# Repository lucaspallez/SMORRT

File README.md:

# SMORRT
Smart Management of Rocket Recovery and Telemetry

Avionics PCB for High-Power Rocketry

Embedded Software for this board available here: https://github.com/lucaspallez/SMORRT_Software
Compatible Ground Station PCB: https://github.com/lucaspallez/GRUND

## Features
- Computation: Teensy 4.1
- Telemetry: RFM95W LoRa Module (with SMA connector)
- IMU: MPU 6050 Breakout
- Barometer: BMP 280 Breakout
- GPS: Ublox NEO-M8J Module (with SMA connector)
- Data logging: 1Mbit FRAM IC + Teensy SD Card slot with locking screw
- Power Output: 4 MOSFET Pyro outputs with E-match detection, 2 Servo compatible (via PWM)
- Battery Management: 2x 1s Li-Ion Battery chargers
- Power Inputs: 2x Redundant 1s Li-Ion Battery connectors + 1x 12V Battery connector for power
- Arming: 1x Main external arm switch + 1x Power out external arm switch
- Status Indicators: 5x User programmable LEDs, 1x Buzzer
- Battery voltage readings

## Changes planned:
- Reduce the physical size to fit in smaller diameter rockets

## Documentation

Designed with KiCAD 5.5

TODO

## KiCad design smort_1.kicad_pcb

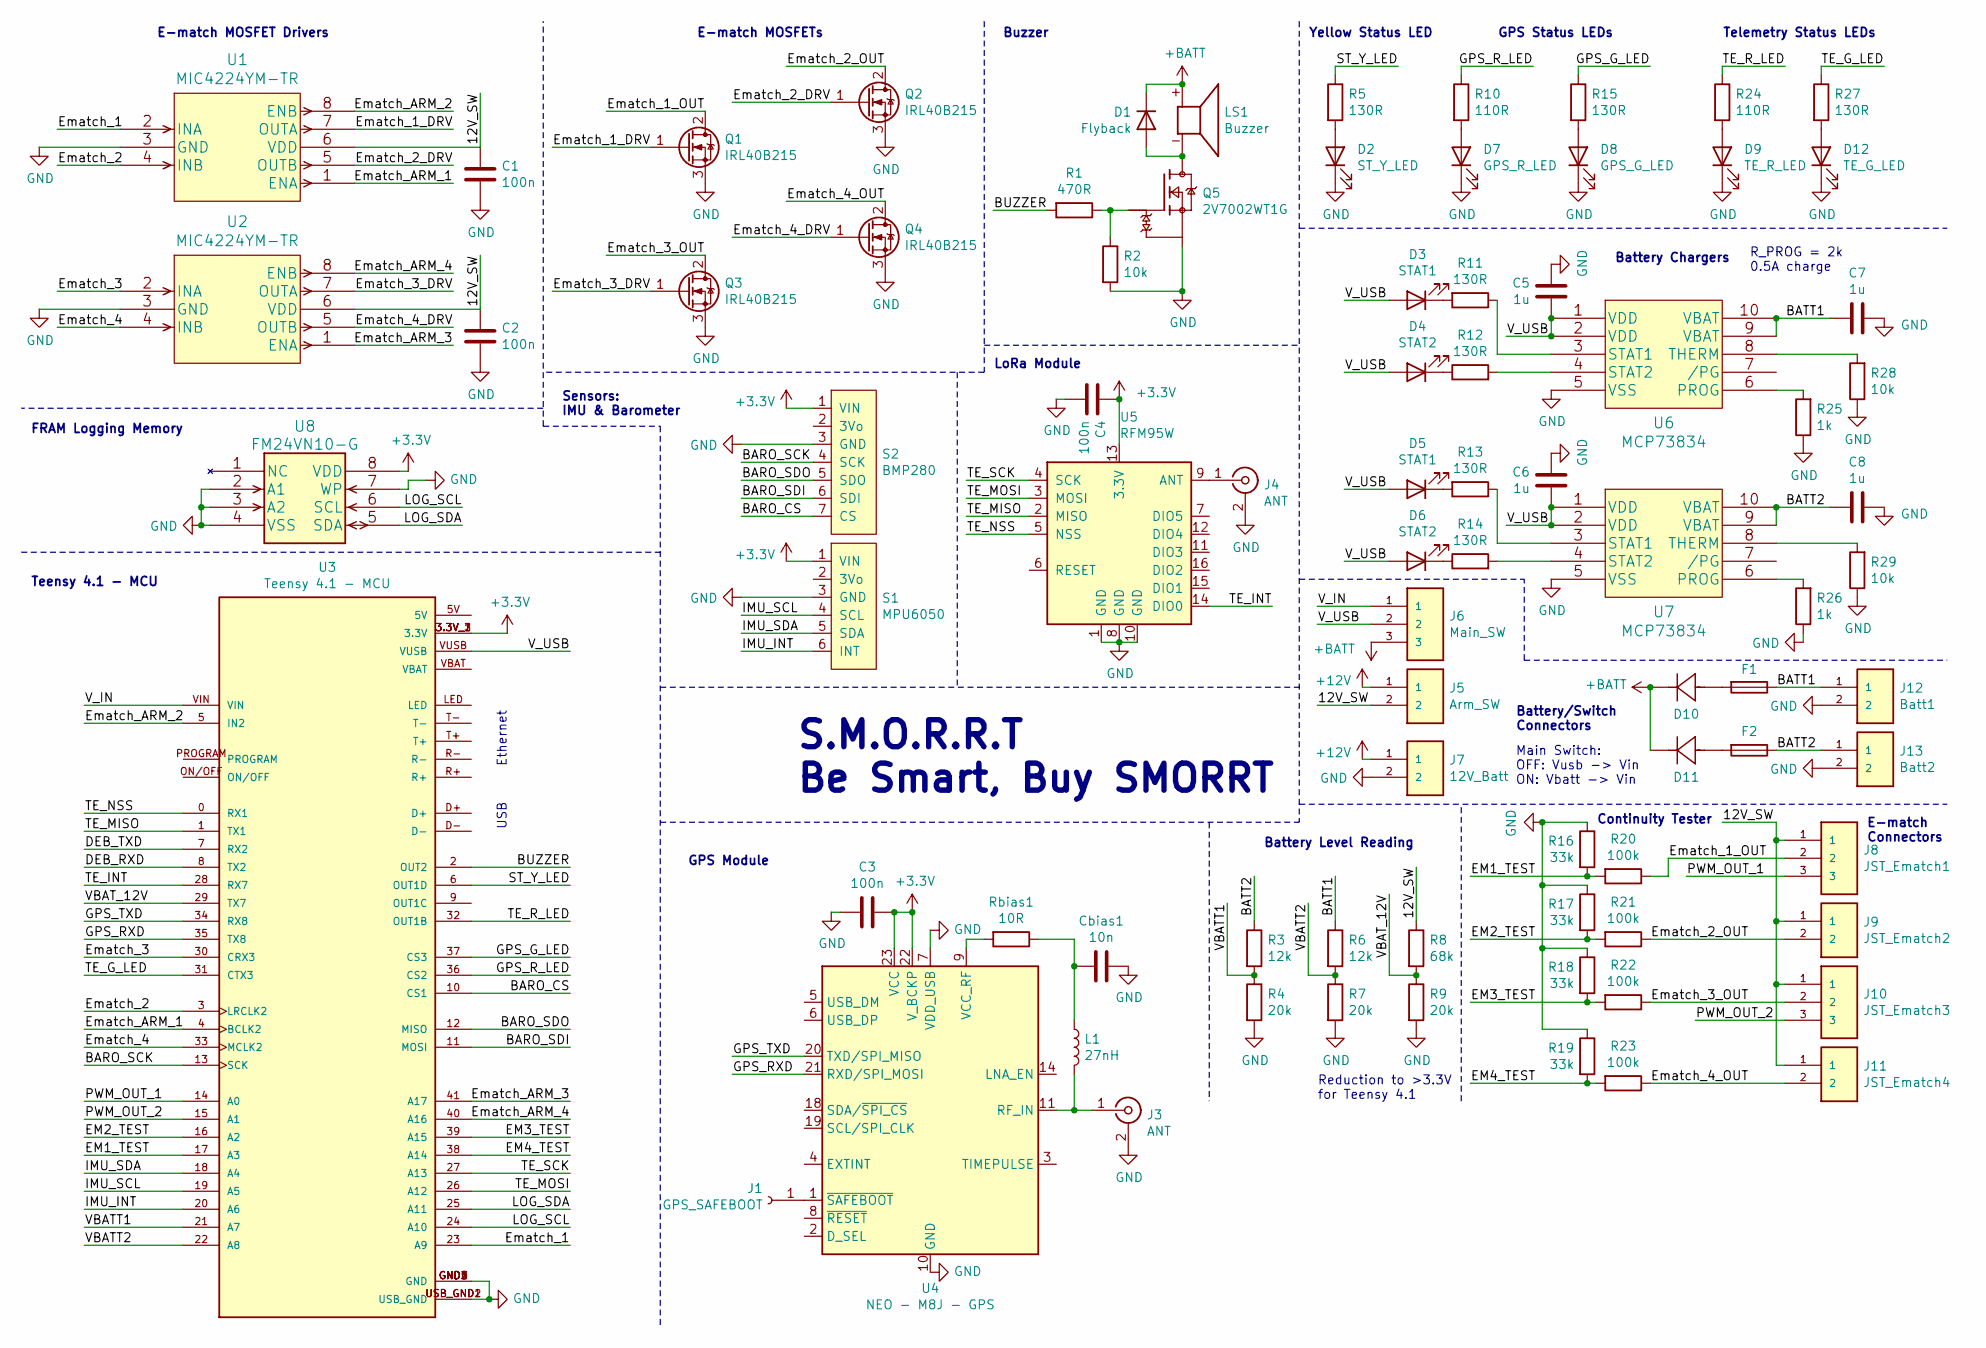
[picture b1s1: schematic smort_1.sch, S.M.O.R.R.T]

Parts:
C1, C2, C3, C4: 100n; C_0805_2012Metric
C5, C6, C7, C8: 1u; C_0805_2012Metric
Cbias1: 10n; C_0805_2012Metric
D1: Flyback; D_SOD-123F
D2: ST_Y_LED; LED_0805_2012Metric_Pad1.15x1.40mm_HandSolder
D3, D5: STAT1; LED_0805_2012Metric_Pad1.15x1.40mm_HandSolder
D4, D6: STAT2; LED_0805_2012Metric_Pad1.15x1.40mm_HandSolder
D7: GPS_R_LED; LED_0805_2012Metric_Pad1.15x1.40mm_HandSolder
D8: GPS_G_LED; LED_0805_2012Metric_Pad1.15x1.40mm_HandSolder
D9: TE_R_LED; LED_0805_2012Metric_Pad1.15x1.40mm_HandSolder
D10: BATT1; LSM115JE3&slash_TR13
D11: BATT2; LSM115JE3&slash_TR13
D12: TE_G_LED; LED_0805_2012Metric_Pad1.15x1.40mm_HandSolder
F1, F2: Fuse; Fuse_0805_2012Metric
J1: GPS_SAFEBOOT; PinHeader_1x01_P2.54mm_Vertical
J3, J4: ANT; LINX_CONSMA020.062-G
J5: Arm_SW; JST_S2B-PH-K-S(LF)(SN)
J6: Main_SW; JST_S3B-PH-K-S(LF)(SN)
J7: 12V_Batt; JST_S2B-PH-K-S(LF)(SN)
J8: JST_Ematch1; JST_S3B-PH-K-S(LF)(SN)
J9: JST_Ematch2; JST_S2B-PH-K-S(LF)(SN)
J10: JST_Ematch3; JST_S3B-PH-K-S(LF)(SN)
J11: JST_Ematch4; JST_S2B-PH-K-S(LF)(SN)
J12: Batt1; JST_S2B-PH-K-S(LF)(SN)
J13: Batt2; JST_S2B-PH-K-S(LF)(SN)
L1: 27nH; L_0805_2012Metric
LS1: Buzzer; CUI_CMI-9605IC-0380T; PARTREV 1.0
Q1, Q2, Q3, Q4: IRL40B215; TO-220F-3_Vertical
Q5: 2V7002WT1G; SOT65P220X100-3N; PARTREV 6
R1: 470R; R_0805_2012Metric
R2, R28, R29: 10k; R_0805_2012Metric
R3, R6: 12k; R_0805_2012Metric
R4, R7, R9: 20k; R_0805_2012Metric
R5, R11, R12, R13, R14, R15, R27: 130R; R_0805_2012Metric
R8: 68k; R_0805_2012Metric
R10, R24: 110R; R_0805_2012Metric
R16, R17, R18, R19: 33k; R_0805_2012Metric
R20, R21, R22, R23: 100k; R_0805_2012Metric
R25, R26: 1k; R_0805_2012Metric
Rbias1: 10R; R_0805_2012Metric
S1: MPU6050; MPU_6050_Breakout
S2: BMP280; BMP_280_Breakout
U1, U2: MIC4224YM-TR
U3: Teensy 4.1 - MCU; MODULE_DEV-16771; PARTREV 4.1
U4: NEO - M8J - GPS; ublox_NEO
U5: RFM95W; HOPERF_RFM9XW_SMD
U6, U7: MCP73834; MCP73834-NVI&slash_UN
U8: FM24VN10-G

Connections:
+3V3: C3.1, C4.1, S1.1 (VIN), S2.1 (VIN), U3.3.3V_1 (3.3V), U3.3.3V_2 (3.3V), U3.3.3V_3 (3.3V), U4.22 (V_BCKP), U4.23 (VCC), U5.13 (3.3V), U8.8 (VDD)
+12V: J5.1, J7.1
+BATT: D1.1 (K), D10.1, D11.1, J6.3, LS1.P
/12V_SW: C1.1, C2.1, J5.2, J8.1, J9.1, J10.1, J11.1, R8.1, U1.6 (VDD), U2.6 (VDD)
/BARO_CS: S2.7 (CS), U3.10 (CS1)
/BARO_SCK: S2.4 (SCK), U3.13 (SCK)
/BARO_SDI: S2.6 (SDI), U3.11 (MOSI)
/BARO_SDO: S2.5 (SDO), U3.12 (MISO)
/BATT1: C7.1, F1.1, J12.1, R6.1, U6.9 (VBAT), U6.10 (VBAT)
/BATT2: C8.1, F2.1, J13.1, R3.1, U7.9 (VBAT), U7.10 (VBAT)
/BUZZER: R1.2, U3.2 (OUT2)
/DEB_RXD: U3.8 (TX2)
/DEB_TXD: U3.7 (RX2)
/EM1_TEST: R16.2, R20.2, U3.17 (A3)
/EM2_TEST: R17.2, R21.2, U3.16 (A2)
/EM3_TEST: R18.2, R22.2, U3.39 (A15)
/EM4_TEST: R19.2, R23.2, U3.38 (A14)
/Ematch_1: U1.2 (INA), U3.23 (A9)
/Ematch_1_DRV: Q1.1 (G), U1.7 (OUTA)
/Ematch_1_OUT: J8.2, Q1.2 (D), R20.1
/Ematch_2: U1.4 (INB), U3.3 (LRCLK2)
/Ematch_2_DRV: Q2.1 (G), U1.5 (OUTB)
/Ematch_2_OUT: J9.2, Q2.2 (D), R21.1
/Ematch_3: U2.2 (INA), U3.30 (CRX3)
/Ematch_3_DRV: Q3.1 (G), U2.7 (OUTA)
/Ematch_3_OUT: J10.2, Q3.2 (D), R22.1
/Ematch_4: U2.4 (INB), U3.33 (MCLK2)
/Ematch_4_DRV: Q4.1 (G), U2.5 (OUTB)
/Ematch_4_OUT: J11.2, Q4.2 (D), R23.1
/Ematch_ARM_1: U1.1 (ENA), U3.4 (BCLK2)
/Ematch_ARM_2: U1.8 (ENB), U3.5 (IN2)
/Ematch_ARM_3: U2.1 (ENA), U3.41 (A17)
/Ematch_ARM_4: U2.8 (ENB), U3.40 (A16)
/GPS_G_LED: R15.1, U3.37 (CS3)
/GPS_RXD: U3.35 (TX8), U4.21 (RXD/SPI_MOSI)
/GPS_R_LED: R10.1, U3.36 (CS2)
/GPS_TXD: U3.34 (RX8), U4.20 (TXD/SPI_MISO)
/IMU_INT: S1.6 (INT), U3.20 (A6)
/IMU_SCL: S1.4 (SCL), U3.19 (A5)
/IMU_SDA: S1.5 (SDA), U3.18 (A4)
/LOG_SCL: U3.24 (A10), U8.6 (SCL)
/LOG_SDA: U3.25 (A11), U8.5 (SDA)
/PWM_OUT_1: J8.3, U3.14 (A0)
/PWM_OUT_2: J10.3, U3.15 (A1)
/ST_Y_LED: R5.1, U3.6 (OUT1D)
/TE_G_LED: R27.1, U3.31 (CTX3)
/TE_INT: U3.28 (RX7), U5.14 (DIO0)
/TE_MISO: U3.1 (TX1), U5.2 (MISO)
/TE_MOSI: U3.26 (A12), U5.3 (MOSI)
/TE_NSS: U3.0 (RX1), U5.5 (NSS)
/TE_R_LED: R24.1, U3.32 (OUT1B)
/TE_SCK: U3.27 (A13), U5.4 (SCK)
/VBATT1: R3.2, R4.1, U3.21 (A7)
/VBATT2: R6.2, R7.1, U3.22 (A8)
/VBAT_12V: R8.2, R9.1, U3.29 (TX7)
/V_IN: J6.1, U3.VIN
/V_USB: C5.1, C6.1, D3.2 (A), D4.2 (A), D5.2 (A), D6.2 (A), J6.2, U3.VUSB, U6.1 (VDD), U6.2 (VDD), U7.1 (VDD), U7.2 (VDD)
GND: C1.2, C2.2, C3.2, C4.2, C5.2, C6.2, C7.2, C8.2, Cbias1.2, D2.1 (K), D7.1 (K), D8.1 (K), D9.1 (K), D12.1 (K), J3.2 (Ext), J4.2 (Ext), J7.2, J12.2, J13.2, Q1.3 (S), Q2.3 (S), Q3.3 (S), Q4.3 (S), Q5.2, R2.2, R4.2, R7.2, R9.2, R16.1, R17.1, R18.1, R19.1, R25.1, R26.1, R28.1, R29.1, S1.3 (GND), S2.3 (GND), U1.3 (GND), U2.3 (GND), U3.GND1 (GND), U3.GND2 (GND), U3.GND3 (GND), U3.GND4 (GND), U3.GND5 (GND), U3.USB_GND1 (USB_GND), U3.USB_GND2 (USB_GND), U4.7 (VDD_USB), U4.10 (GND), U4.12 (GND), U4.13 (GND), U4.24 (GND), U5.1 (GND), U5.8 (GND), U5.10 (GND), U6.5 (VSS), U7.5 (VSS), U8.2 (A1), U8.3 (A2), U8.4 (VSS), U8.7 (WP)
unnamed: Cbias1.1, L1.1, Rbias1.1
unnamed: D1.2 (A), LS1.N, Q5.3
unnamed: D2.2 (A), R5.2
unnamed: D3.1 (K), R11.2
unnamed: D4.1 (K), R12.1
unnamed: D5.1 (K), R13.2
unnamed: D6.1 (K), R14.1
unnamed: D7.2 (A), R10.2
unnamed: D8.2 (A), R15.2
unnamed: D9.2 (A), R24.2
unnamed: D10.2, F1.2
unnamed: D11.2, F2.2
unnamed: D12.2 (A), R27.2
unnamed: J1.1, U4.1 (~SAFEBOOT)
unnamed: J3.1 (In), L1.2, U4.11 (RF_IN)
unnamed: J4.1 (In), U5.9 (ANT)
unnamed: Q5.1, R1.1, R2.1
unnamed: R11.1, U6.3 (STAT1)
unnamed: R12.2, U6.4 (STAT2)
unnamed: R13.1, U7.3 (STAT1)
unnamed: R14.2, U7.4 (STAT2)
unnamed: R25.2, U6.6 (PROG)
unnamed: R26.2, U7.6 (PROG)
unnamed: R28.2, U6.8 (THERM)
unnamed: R29.2, U7.8 (THERM)
unnamed: Rbias1.2, U4.9 (VCC_RF)

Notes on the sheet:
Telemetry Status LEDs
GPS Status LEDs
Yellow Status LED
E-match MOSFET Drivers
E-match MOSFETs
LoRa Module
Ethernet
USB
Teensy 4.1 - MCU
GPS Module
Battery Chargers
Main Switch: OFF: Vusb -> Vin ON: Vbatt -> Vin
Battery/Switch Connectors
Buzzer
Sensors: IMU & Barometer
R_PROG = 2k 0.5A charge
Battery Level Reading
Reduction to >3.3V for Teensy 4.1
FRAM Logging Memory
S.M.O.R.R.T Be Smart, Buy SMORRT
E-match Connectors
Continuity Tester

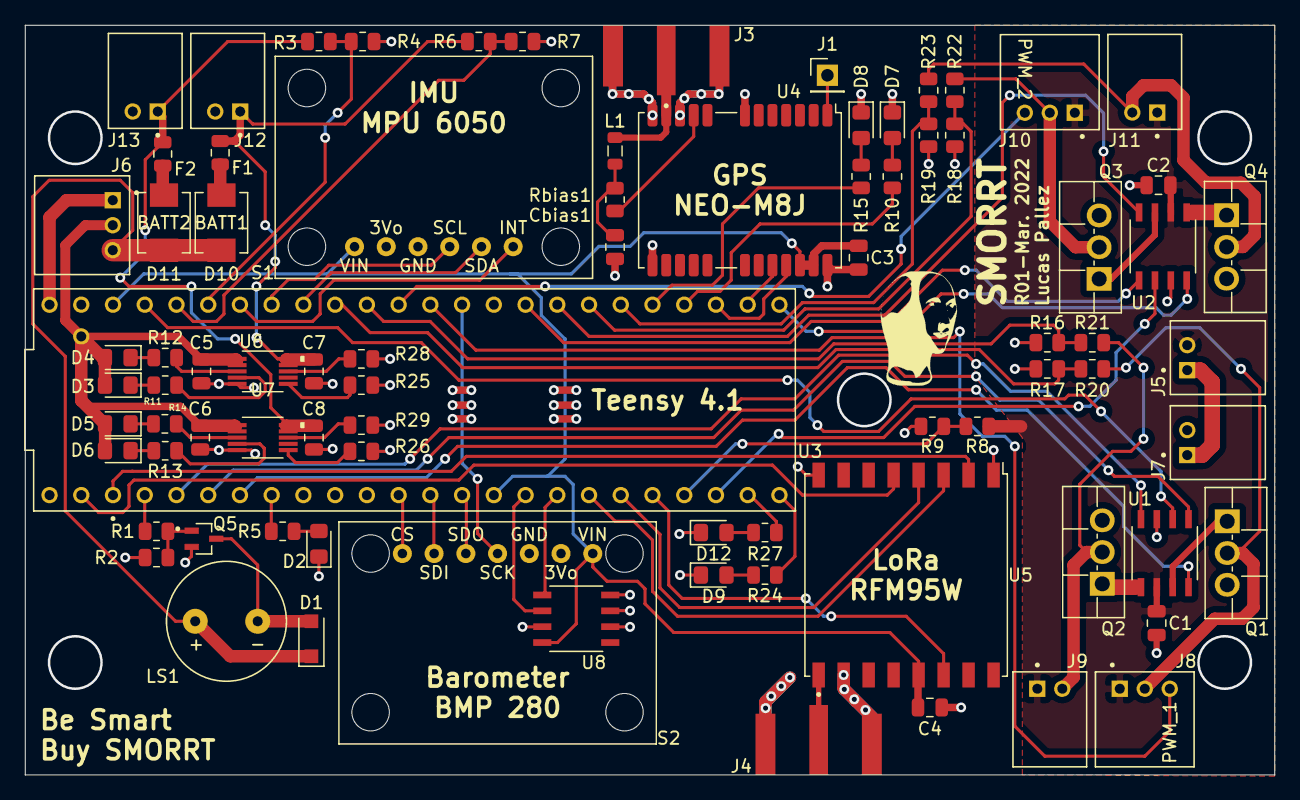
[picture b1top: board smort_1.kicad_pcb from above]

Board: 2 copper layers, 100.0 x 60.0 mm, 82 parts (0 on the bottom side), 82 nets.

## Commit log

2022-03-28 Initial PCB commit

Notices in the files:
parts and their libraries:
Copyright 2021 Accelerated Designs. All rights reserved.
